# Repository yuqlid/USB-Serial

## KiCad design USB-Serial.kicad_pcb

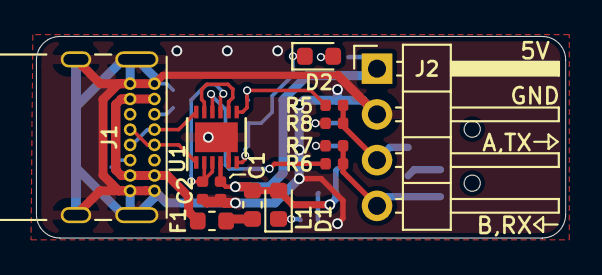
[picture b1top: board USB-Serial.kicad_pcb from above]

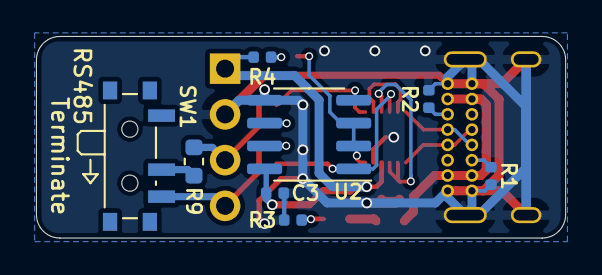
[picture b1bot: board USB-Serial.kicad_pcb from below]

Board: 2 copper layers, 29.4 x 11.2 mm, 21 parts (8 on the bottom side), 20 nets.

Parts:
C1, C2, C3: 0.1u; C_0402_1005Metric
D1, D2: LED; LED_0603_1608Metric
F1: Fuse; Fuse_0603_1608Metric
J1: USB_C_Receptacle_USB2.0; USB_C_Receptacle_GCT_USB4085
J2: Conn_01x04; PinHeader_1x04_P2.54mm_Horizontal
L1: L; L_0603_1608Metric
R1, R2: 5.1k; R_0402_1005Metric
R3, R4: 1k; R_0402_1005Metric
R5, R6: 22; R_0402_1005Metric
R7, R8: 0; R_0402_1005Metric
R9: 120; R_0603_1608Metric
SW1: SW_DPDT_x2; SW_SPDT_PCM12
U1: FT234XD; DFN-12-1EP_3x3mm_P0.45mm_EP1.66x2.38mm
U2: SP3481CN; SOIC-8_3.9x4.9mm_P1.27mm

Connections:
GND: C1.2, C2.2, C3.2, J1.A1, J1.A12, J1.B1, J1.B12, J1.S1, J2.2, R1.2, R2.2, R3.2, U1.5, U1.13, U2.5
unnamed: C1.1, C3.1, D1.2, J2.1, L1.2, R4.1, U1.4, U2.8
unnamed: C2.1, U1.2, U1.3, U1.9
unnamed: D1.1, R3.1
unnamed: D2.1, U1.6, U2.2, U2.3
unnamed: D2.2, R4.2
unnamed: F1.1, L1.1
unnamed: F1.2, J1.A4, J1.A9, J1.B4, J1.B9
unnamed: J1.A5, R2.1
unnamed: J1.A6, J1.B6, U1.12
unnamed: J1.A7, J1.B7, U1.1
unnamed: J1.B5, R1.1
unnamed: J2.3, R5.2, R8.2, R9.1
unnamed: J2.4, R6.2, R7.2, SW1.3
unnamed: R5.1, U1.7, U2.4
unnamed: R6.1, U1.10, U2.1
unnamed: R7.1, U2.7
unnamed: R8.1, U2.6
unnamed: R9.2, SW1.2
unnamed: U1.8, U1.11

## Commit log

2019-11-04 Create LICENSE
